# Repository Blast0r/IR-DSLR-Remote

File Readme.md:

InfraRed Remote for (most) DSLR-Cameras

Based on http://www.instructables.com/id/Camera-remote-control-and-timelapse/ by andyk75
Licensed under CC BY-NC-SA 2.5

I have to add an schematic for this Project...

List of material:
 * 3 Push- Buttons (Reset, Intervalometer, Shutterrelease/Start)
 * BatteryHolder
 * Red LED
 * Infrared LED
 * BC 337 Transistor
 * ATtiny85
 * IC-Holder
 * Base Resistor 150 Ohms
 * LED resistor 1kOhms (or even higher, the LED was very bright)
 
Picture:

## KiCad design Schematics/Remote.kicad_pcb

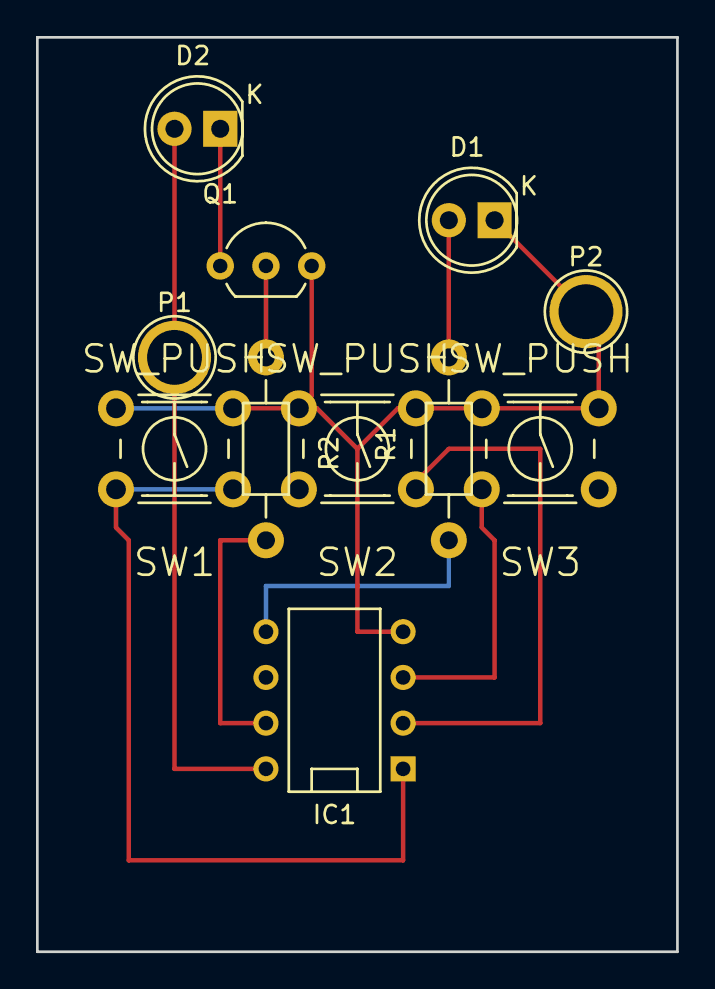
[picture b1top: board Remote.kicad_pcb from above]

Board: 2 copper layers, 35.6 x 50.8 mm, 11 parts (0 on the bottom side), 10 nets.

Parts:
D1: LED; LED-5MM
D2: IR_LED; LED-5MM
IC1: meinTiny85; DIP-8__300
P1, P2: CONN_01X01; 1pin
Q1: Q_NPN_CBE; TO-92_Inline_Wide
R1: 1k; Resistor_Horizontal_RM10mm
R2: 150; Resistor_Horizontal_RM10mm
SW1, SW2, SW3: SW_PUSH; JTP-1130

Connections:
+BATT: D2.2, IC1.8, P1.1
GND: D1.1, IC1.4, P2.1, Q1.3, SW1.1, SW2.1, SW3.1
unnamed: D1.2, R1.2
unnamed: D2.1, Q1.1
unnamed: IC1.1, SW1.2
unnamed: IC1.2, SW2.2
unnamed: IC1.3, SW3.2
unnamed: IC1.5, R1.1
unnamed: IC1.7, R2.2
unnamed: Q1.2, R2.1

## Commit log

2014-12-05 .gitignore added
2014-12-05 picture added, readme changed
2014-12-05 List of materials added
2014-12-05 picture linked
2014-12-05 renamed Readme
2014-12-26 Tv b gone ordner ausgenommen gitignore..
2015-01-05 Moved lighting of status LED while sending into the triggerrelease function
2015-01-05 Added Comment Sony shutterrelease function
2015-01-17 kommentare zu sony cmds hinzgefügt
2015-01-18 comment to different Sony CMD
2015-09-16 Begin of Schematics and maybe PCB
2015-09-17 schematic and PCB Layout done..
